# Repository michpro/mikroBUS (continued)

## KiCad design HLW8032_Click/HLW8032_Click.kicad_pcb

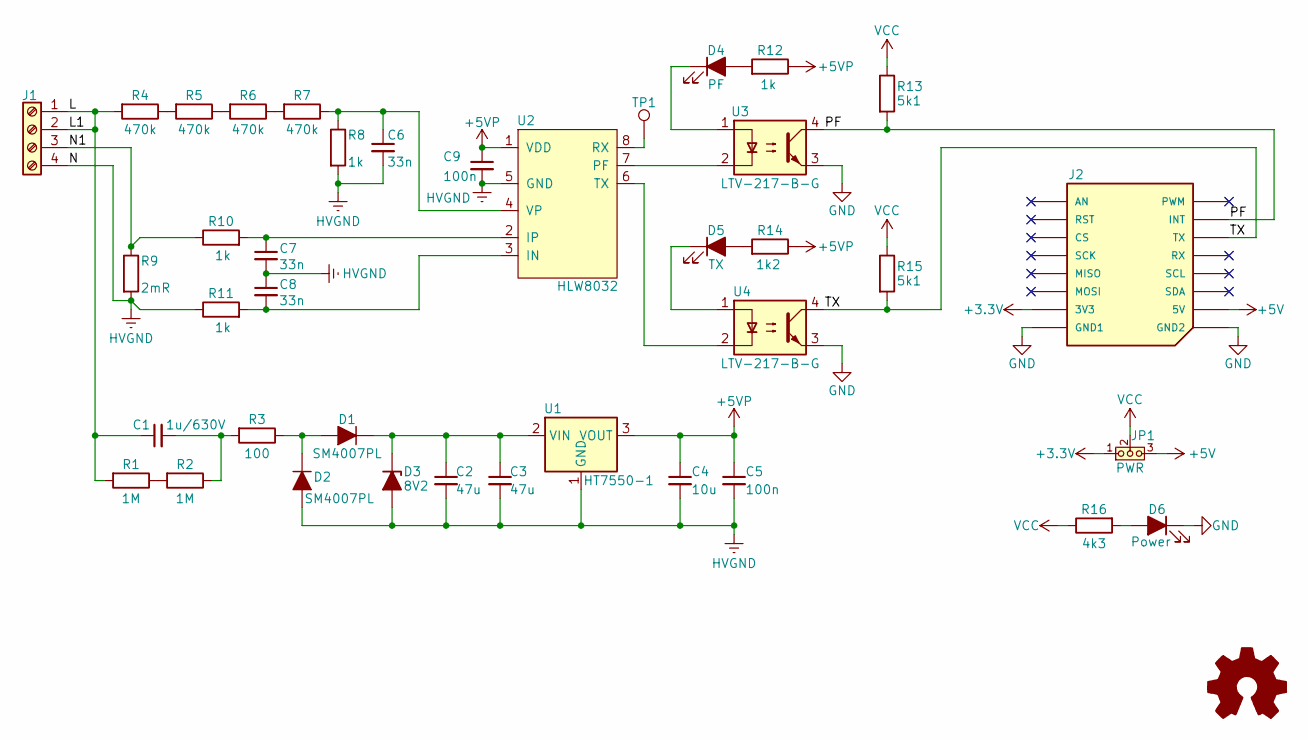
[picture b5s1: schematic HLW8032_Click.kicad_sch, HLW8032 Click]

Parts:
C1: 1u/630V; C_2220_5750Metric; LCSC C784102
C2, C3: 47u; C_1210_3225Metric; LCSC C5440143
C4: 10u; C_0805_2012Metric; LCSC C15850
C5, C9: 100n; C_0805_2012Metric; LCSC C49678
C6, C7, C8: 33n; C_0805_2012Metric; LCSC C1739
D1, D2: SM4007PL; D_SOD-123FL; LCSC C64898
D3: 8V2; D_SOD-123; LCSC C22399882
D4: PF; LED_0805_2012Metric; LCSC C2296
D5: TX; LED_0805_2012Metric; LCSC C84256
D6: Power; LED_0805_2012Metric; LCSC C2297
J1: 2EDGR-5.08-04P; LCSC C5187975
J2: HLW8032 Click v${REVISION} by MPro; mikroBUS_module_L; LCSC -----
JP1: PWR; PinHeader_1x03_P2.54mm_Vertical; LCSC C5383112
LOGO1: Logo_Open_Hardware_Small; OSHW-Logo2_7.3x6mm_SilkScreen
R1, R2: 1M; R_1206_3216Metric; LCSC C17927
R3: 100; R_2512_6332Metric; LCSC C5126189
R4, R5, R6, R7: 470k; R_0805_2012Metric; LCSC C17709
R8, R10, R11: 1k; R_0805_2012Metric; LCSC C17513
R9: 2mR; R_2512_6332Metric_HP; LCSC C316197
R12: 1k; R_0603_1608Metric; LCSC C21190
R13, R15: 5k1; R_0603_1608Metric; LCSC C23186
R14: 1k2; R_0603_1608Metric; LCSC C22765
R16: 4k3; R_0805_2012Metric; LCSC C17667
TP1: RX; TestPoint_Pad_D2.0mm; LCSC ------
U1: HT7550-1; SOT-89-3; LCSC C16106
U2: HLW8032; SOP-8_3.9x4.9mm_P1.27mm; LCSC C128023
U3, U4: LTV-217-B-G; SOP-4_4.4x2.6mm_P1.27mm; LCSC C115450

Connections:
+3.3V: J2.P7 (3V3), JP1.1 (A)
+5V: J2.P10 (5V), JP1.3 (B)
+5VP: C4.1, C5.1, C9.1, R12.1, R14.1, U1.3 (VOUT), U2.1 (VDD)
/L: C1.1, J1.1, J1.2, R1.2, R4.2
/N1: J1.3, R9.1, R10.1
/PF: J2.P15 (INT), R13.2, U3.4
/TX: J2.P14 (TX), R15.2, U4.4
GND: D6.1 (K), J2.P8 (GND1), J2.P9 (GND2), U3.3, U4.3
HVGND: C2.2, C3.2, C4.2, C5.2, C6.2, C7.2, C8.1, C9.2, D2.2 (A), D3.2 (A), J1.4, R8.2, R9.2, R11.1, U1.1 (GND), U2.5 (GND)
unnamed: C1.2, R2.1, R3.2
unnamed: D1.2 (A), D2.1 (K), R3.1
unnamed: C2.1, C3.1, D1.1 (K), D3.1 (K), U1.2 (VIN)
unnamed: D4.2 (A), R12.2
unnamed: D4.1 (K), U3.1
unnamed: D5.2 (A), R14.2
unnamed: D5.1 (K), U4.1
unnamed: D6.2 (A), R16.2
unnamed: R1.1, R2.2
unnamed: R4.1, R5.2
unnamed: R5.1, R6.2
unnamed: R6.1, R7.2
unnamed: C8.2, R11.2, U2.3 (IN)
unnamed: C7.1, R10.2, U2.2 (IP)
unnamed: U2.7 (PF), U3.2
unnamed: TP1.1, U2.8 (RX)
unnamed: U2.6 (TX), U4.2
unnamed: C6.1, R7.1, R8.1, U2.4 (VP)
VCC: JP1.2 (C), R13.1, R15.1, R16.1

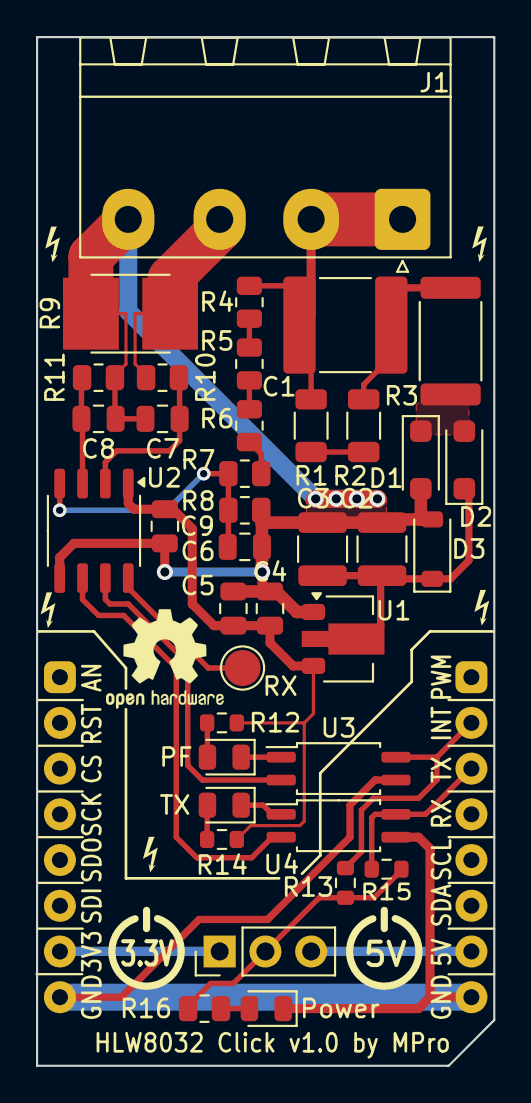
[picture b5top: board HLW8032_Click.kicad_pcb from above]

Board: 2 copper layers, 25.4 x 57.1 mm, 40 parts (0 on the bottom side), 28 nets.

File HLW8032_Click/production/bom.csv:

Designator,Footprint,Quantity,Value,LCSC Part #
C1,2220,1,1u/630V,C784102
"C2, C3",1210,2,47u,C5440143
C4,0805,1,10u,C15850
"C5, C9",0805,2,100n,C49678
"C6, C7, C8",0805,3,33n,C1739
"D1, D2",D_SOD-123FL,2,SM4007PL,C64898
D3,D_SOD-123,1,8V2,C22399882
D4,0805,1,PF,C2296
D5,0805,1,TX,C84256
D6,0805,1,Power,C2297
J1,2EDGR-5.08-04P,1,2EDGR-5.08-04P,C5187975
JP1,PinHeader_1x03_P2.54mm_Vertical,1,PWR,C5383112
"R1, R2",1206,2,1M,C17927
"R10, R11, R8",0805,3,1k,C17513
R12,0603,1,1k,C21190
"R13, R15",0603,2,5k1,C23186
R14,0603,1,1k2,C22765
R16,0805,1,4k3,C17667
R3,2512,1,100,C5126189
"R4, R5, R6, R7",0805,4,470k,C17709
R9,2512,1,2mR,C316197
U1,SOT-89-3,1,HT7550-1,C16106
U2,SOP-8_3.9x4.9mm_P1.27mm,1,HLW8032,C128023
"U3, U4",SOP-4_4.4x2.6mm_P1.27mm,2,LTV-217-B-G,C115450

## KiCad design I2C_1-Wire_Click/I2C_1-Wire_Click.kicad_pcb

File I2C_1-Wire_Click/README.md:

# **I²C to 1-Wire Click**

- [**I²C to 1-Wire Click**](#ic-to-1-wire-click)
  - [**Overview**](#overview)
    - [**Features**](#features)
  - [**Schematic diagram**](#schematic-diagram)
  - [**Module visualisation**](#module-visualisation)
  - [**Assembly**](#assembly)
  - [**Production files**](#production-files)
  - [**Configuration**](#configuration)
      - [**Note**](#note)
  - [**Reporting bugs**](#reporting-bugs)
  - [**License**](#license)
  - [**Support**](#support)

---

## **Overview**
The I²C to 1-Wire Click board is a compact module designed to enable communication between a microcontroller with an I²C interface and 1-Wire devices. Built around the DS2482-100 I²C to 1-Wire bridge IC from Analog Devices, this board simplifies the integration of 1-Wire devices into I²C-based systems. It adheres to the MikroBUS™ standard, ensuring compatibility with a wide range of host systems that support Click boards.

### **Features**
* **I²C to 1-Wire Conversion**: Utilizes the DS2482-100 chip for seamless protocol bridging.
* **MikroBUS™ Compatibility**: Equipped with a MikroBUS™ connector for easy integration into host systems.
* **1-Wire Interface**: Features a 3-pin connector for connecting 1-Wire devices.
* **Power LED**: Visual indicator for power status.
* **Flexible Power Supply**: Supports operation at both 3.3V and 5V.
* **Configurable Options**: Includes solder jumpers for I²C pull-up resistors and address selection.

---

## **Schematic diagram**

## **Module visualisation**
(click on the image to see the 3D model)
<p align="center"></p>

## **Assembly**
[Interactive BOM and placement](https://michpro.github.io/mikroBUS/I2C_1-Wire_Click/docs/ibom.html)

## **Production files**
Production files can be found [**here**](./production/).

## **Configuration**
The board offers solder jumpers for customization:
* **JP1**: Enables the 2.2kΩ pull-up resistor on SCL when closed (default: open).
* **JP2**: Enables the 2.2kΩ pull-up resistor on SDA when closed (default: open).
* **JP4, JP5**: Configure the I²C address of the DS2482-100 by connecting AD1 and AD0 to V<sub>CC</sub> or GND.

#### **Note**
To enable a pull-up feature (JP1, JP2), solder the jumper pads closed. Ensure the host system’s I²C bus requirements align with the configured settings (e.g., pull-up resistors may already exist on the host).

---

## **Reporting bugs**

[Create an issue on GitHub](https://github.com/michpro/mikroBUS/issues)

---

## **License**
Copyright © 2023-2025 Michal Protasowicki

This project is released under CERN Open Hardware Licence Version 2 - Permissive.

---

## **Support**
If You find my projects interesting and You wanted to support my work, You can give me a cup of coffee or a keg of beer :)

&nbsp;&nbsp;&nbsp;&nbsp;&nbsp;&nbsp;&nbsp;&nbsp;&nbsp;&nbsp;

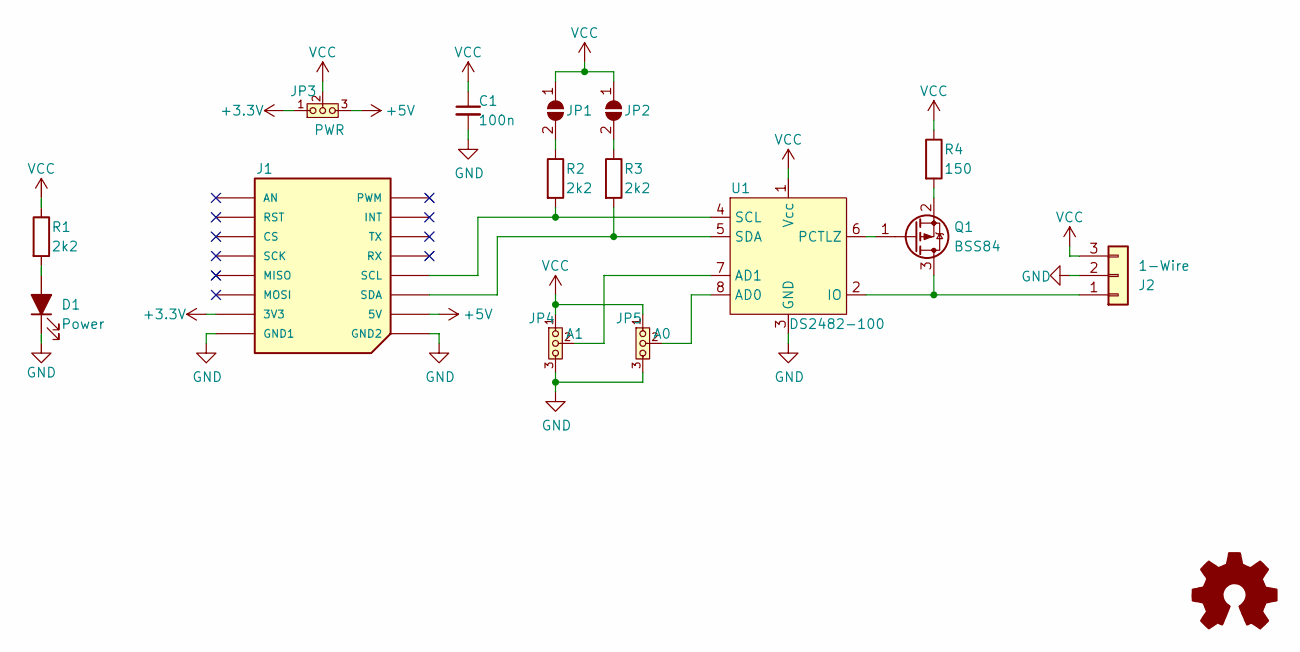
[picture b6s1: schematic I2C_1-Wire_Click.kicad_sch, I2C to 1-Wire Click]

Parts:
C1: 100n; C_0805_2012Metric; LCSC C49678
D1: Power; LED_0805_2012Metric; LCSC C2296
J1: I^{2}C to 1-Wire Click v${REVISION} by MPro; mikroBUS_module_M; LCSC -----
J2: 1-Wire; PinHeader_1x03_P2.54mm_Horizontal; LCSC -----
JP1: SCL; SolderJumper-2_P1.3mm_Open_TrianglePad1.0x1.5mm; LCSC -----
JP2: SDA; SolderJumper-2_P1.3mm_Open_TrianglePad1.0x1.5mm; LCSC -----
JP3: PWR; PinHeader_1x03_P2.54mm_Vertical; LCSC -----
JP4: A1; PinHeader_1x03_P2.54mm_Vertical; LCSC -----
JP5: A0; PinHeader_1x03_P2.54mm_Vertical; LCSC -----
LOGO1: Logo_Open_Hardware_Small; OSHW-Logo2_7.3x6mm_SilkScreen
Q1: BSS84; SOT-23; LCSC C8492
R1, R2, R3: 2k2; R_0805_2012Metric; LCSC C17520
R4: 150; R_0805_2012Metric; LCSC C17471
U1: DS2482-100; SO-8_3.9x4.9mm_P1.27mm; LCSC C143306

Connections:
+3.3V: J1.P7 (3V3), JP3.1 (A)
+5V: J1.P10 (5V), JP3.3 (B)
GND: C1.2, D1.1 (K), J1.P8 (GND1), J1.P9 (GND2), J2.2, JP4.3 (B), JP5.3 (B), U1.3 (GND)
unnamed: D1.2 (A), R1.2
unnamed: J1.P12 (SCL), R2.2, U1.4 (SCL)
unnamed: J1.P11 (SDA), R3.2, U1.5 (SDA)
unnamed: J2.1, Q1.3 (D), U1.2 (IO)
unnamed: JP1.2 (B), R2.1
unnamed: JP2.2 (B), R3.1
unnamed: JP4.2 (C), U1.7 (AD1)
unnamed: JP5.2 (C), U1.8 (AD0)
unnamed: Q1.1 (G), U1.6 (PCTLZ)
unnamed: Q1.2 (S), R4.2
VCC: C1.1, J2.3, JP1.1 (A), JP2.1 (A), JP3.2 (C), JP4.1 (A), JP5.1 (A), R1.1, R4.1, U1.1 (Vcc)

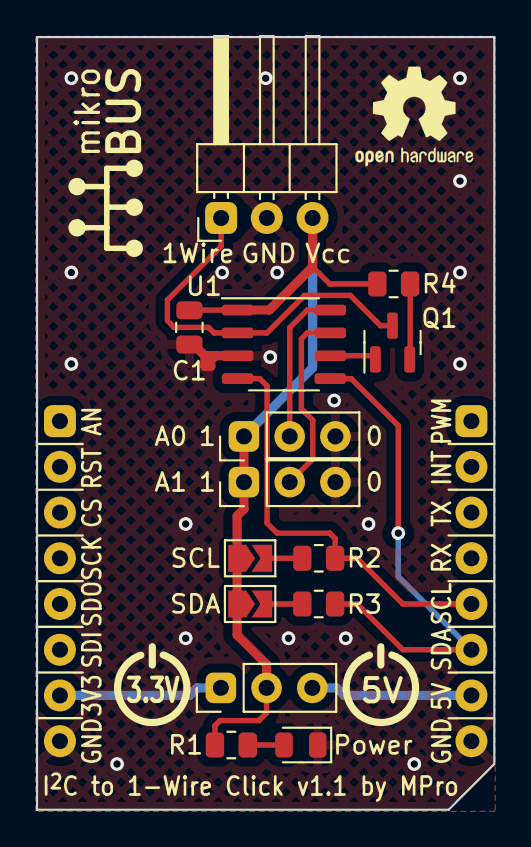
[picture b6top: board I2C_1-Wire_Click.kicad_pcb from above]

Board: 2 copper layers, 25.4 x 42.9 mm, 19 parts (0 on the bottom side), 14 nets.

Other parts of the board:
REF1: LOGO; Logo_Power_3V3
REF2: LOGO; Logo_Power_5V
REF3: mikroBUS_logo_text

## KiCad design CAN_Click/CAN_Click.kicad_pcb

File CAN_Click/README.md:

# **CAN Click**

- [**CAN Click**](#can-click)
  - [**Overview**](#overview)
    - [**Features**](#features)
  - [**Schematic diagram**](#schematic-diagram)
  - [**Module visualisation**](#module-visualisation)
  - [**Assembly**](#assembly)
  - [**Production files**](#production-files)
  - [**Testing out the hardware**](#testing-out-the-hardware)
    - [1. Hardware Setup](#1-hardware-setup)
      - [MikroBUS™ Slot Configuration](#mikrobus-slot-configuration)
      - [CAN Bus Connection](#can-bus-connection)
      - [Additional Notes](#additional-notes)
    - [2. Software Setup](#2-software-setup)
      - [Prerequisites](#prerequisites)
      - [Library Installation](#library-installation)
      - [Code Upload](#code-upload)
      - [Serial Monitor](#serial-monitor)
      - [Additional Notes](#additional-notes-1)
    - [3. Operation](#3-operation)
      - [CAN Initialization](#can-initialization)
      - [Message Transmission](#message-transmission)
      - [Message Reception](#message-reception)
    - [4. Additional Notes](#4-additional-notes)
      - [CAN Configuration](#can-configuration)
      - [Troubleshooting](#troubleshooting)
  - [**Reporting bugs**](#reporting-bugs)
  - [**License**](#license)
    - [**Hardware**](#hardware)
    - [**Software**](#software)
  - [**Support**](#support)

---

## **Overview**
The CAN Click is a compact add-on board designed to integrate Controller Area Network (CAN) bus communication into microcontroller-based systems. It adheres to the mikroBUS™ standard, enabling seamless connection to any host board with a mikroBUS™ socket. The board features the MCP2515 standalone CAN controller and the COS1042T/3 high-speed CAN transceiver, providing a robust and reliable CAN bus interface.

### **Features**
* **CAN Controller**: MCP2515 with SPI interface for communication with the host microcontroller.
* **CAN Transceiver**: COS1042T/3 supporting high-speed CAN communication.
* **Crystal Oscillator**: 12 MHz crystal for precise timing of the MCP2515.
* **Power Supply**: Configurable for 3.3V or 5V operation via jumper (JP1).
* **Interfaces**: SPI communication lines, interrupt pin (INT), and reset pin (RST) via mikroBUS™; CAN bus connection via a 3-position spring terminal.
* **Indicators**: Power/activity LED (D1).
* **Termination**: Optional CAN bus termination resistor (120Ω) via jumper (JP2).

---

## **Schematic diagram**

## **Module visualisation**
(click on the image to see the 3D model)
<p align="center"></p>

## **Assembly**
[Interactive BOM and placement](https://michpro.github.io/mikroBUS/CAN_Click/docs/ibom.html)

## **Production files**
Production files can be found [**here**](./production/).

---

## **Testing out the hardware**
Below are step-by-step instructions to set up and run the provided Arduino UNO code [test_sw.ino](./test_sw/test_sw.ino) for bidirectional CAN bus communication using the MCP2515 module. The code enables periodic transmission of a 3-byte counter message with an extended CAN ID (0x0BB0DEEF) at 1000 kbps and simultaneous reception of incoming CAN messages, both logged to the serial monitor.

### 1. Hardware Setup

#### MikroBUS™ Slot Configuration
The code supports two MikroBUS™ slot configurations for connecting the MCP2515 CAN bus module to the Arduino UNO.<br>Select one slot and connect the module to the corresponding pins:

* **MOSI**: Pin 11
* **MISO**: Pin 12
* **SCK**: Pin 13
* **For Slot 1** (default, `MIKROBUS_SLOT` set to `1`):
  * **SPI Chip Select (CS)**: Pin 10
  * **CAN Interrupt (INT)**: Pin 3
  * **CAN Standby**: Pin 6

* **For Slot 2** (modify `MIKROBUS_SLOT` to `2` in the code):
  * **SPI Chip Select (CS)**: Pin 7
  * **CAN Interrupt (INT)**: Pin 2
  * **CAN Standby**: Pin 5
  
You can also use the [Arduino UNO Click Shield](../Arduino_UNO_click_shield/README.md) or [BluePill Base Board](../BluePill_base/README.md) for the connection.

#### CAN Bus Connection
* Connect the MCP2515 module’s CAN_H and CAN_L pins to the CAN bus.
* Ensure the CAN bus is properly terminated with 120Ω resistors at both ends.
* Connect the CAN bus to another CAN device configured to operate at 1000 kbps and capable of handling extended CAN IDs.

#### Additional Notes
* Verify all connections (SPI: MOSI, MISO, SCK; power: 5V, GND) between the Arduino UNO and the MCP2515 module are secure.

---

### 2. Software Setup

#### Prerequisites
* Use an Arduino board with AVR architecture (e.g., Arduino UNO), as the code includes a check (`ARDUINO_ARCH_AVR`) to enforce this.

#### Library Installation
By default, all additional libraries are provided with the program and placed in the `src` folder of the project.
* **`mcp2515_can`**: For CAN bus communication with the MCP2515 module.
  * Available via the [Arduino Library](https://docs.arduino.cc/libraries/can_bus_shield/) Manager or [GitHub](https://github.com/Seeed-Studio/Seeed_Arduino_CAN).
* **`SimplestTimer`**: For timing the periodic message transmissions.

#### Code Upload
1. Open the provided `test_sw.ino` file in the Arduino IDE.
2. Verify the `MIKROBUS_SLOT` definition (`1` or `2`) matches your hardware configuration.
3. Upload the code to the Arduino UNO.

#### Serial Monitor
* Open the Arduino IDE’s Serial Monitor.
* Set the baud rate to **115200** to view the output.

#### Additional Notes
* The libraries used in this project are marked as independent of the µC architecture, so after removing the guard and adjusting the pin mapping, you can try to run this software on µCs other than AVR, e.g. on STM32.

---

### 3. Operation

#### CAN Initialization
* Upon startup, the code initializes the MCP2515 module at **1000 kbps** with a 12 MHz clock (`MCP_12MHz`).
* If initialization fails, the serial monitor displays `"CAN init fail, retry..."` and retries every second until successful.
* Once initialized, `"CAN init OK!"` is printed.

#### Message Transmission
* Every **2.5 seconds** (`CAN_MSG_SEND_PERIOD = 2500ms`), the Arduino sends a 3-byte CAN message:
  * **CAN ID**: `0x0BB0DEEF` (extended ID format).
  * **Data**: A 24-bit counter (`txCounter`) split into three bytes (MSB to LSB), incrementing with each transmission.
* Successful transmissions are logged to the serial monitor in the format:
  ```
  TX ID: 0x0BB0DEEF  data: 0x00 0x00 0x01
  ```

#### Message Reception
* The Arduino continuously checks for incoming CAN messages.
* Received messages are logged to the serial monitor with their CAN ID and data in hexadecimal format, e.g.:
  ```
  RX ID: 0x12345678  data: 0xAA 0xBB 0xCC
  ```
* If a message has no data, only the ID is printed.

---

### 4. Additional Notes

#### CAN Configuration
* **Speed**: 1000 kbps (`CAN_1000KBPS`).
* **ID Type**: Extended IDs (`CAN_EXTENDED_ID = 1`).
* **Frame Format**: Data Frame (`CAN_STANDARD_FRAME = 0`).
* Ensure the connected CAN device matches these settings.

#### Troubleshooting
* **No Output**: Check Serial Monitor baud rate (115200), library installation, and hardware connections.
* **CAN Init Fails**: Verify pin connections, power supply, and CAN bus termination.
* **No Communication**: Confirm the other CAN device is operational and configured correctly.

---

*By following these instructions, you should successfully set up and run the CAN bus test project on your Arduino UNO with the mikroBUS™ CAN Click. The system will transmit an incrementing counter every 2.5 seconds and display both sent and received messages on the serial monitor.*

---

## **Reporting bugs**

[Create an issue on GitHub](https://github.com/michpro/mikroBUS/issues)

---

## **License**
Copyright © 2025 Michal Protasowicki

### **Hardware**
  * Hardware part of this project is released under CERN Open Hardware Licence Version 2 - Permissive.

### **Software**
  * Software part of this project is released under MIT Licence.

---

## **Support**
If You find my projects interesting and You wanted to support my work, You can give me a cup of coffee or a keg of beer :)

&nbsp;&nbsp;&nbsp;&nbsp;&nbsp;&nbsp;&nbsp;&nbsp;&nbsp;&nbsp;

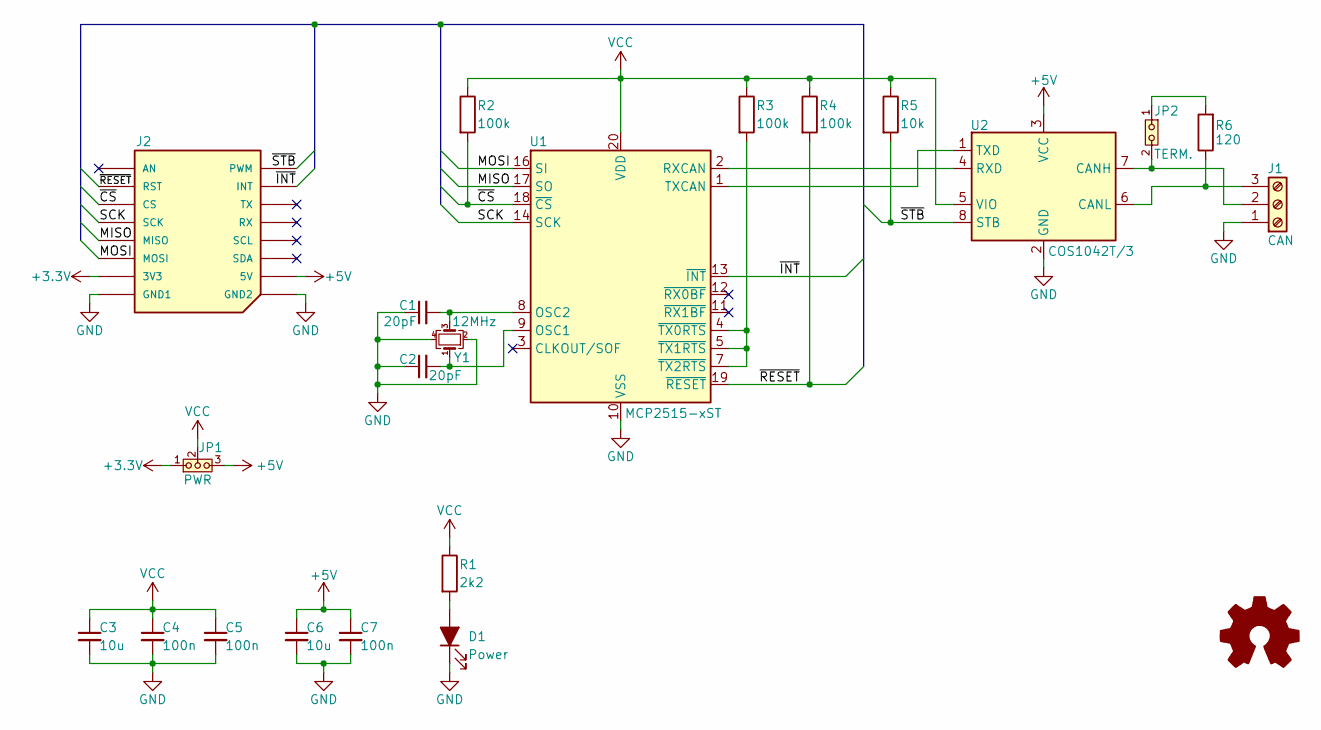
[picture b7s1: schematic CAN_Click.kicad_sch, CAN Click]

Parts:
C1, C2: 20pF; C_0805_2012Metric; LCSC C1798
C3, C6: 10u; C_0805_2012Metric; LCSC C15850
C4, C5, C7: 100n; C_0805_2012Metric; LCSC C49678
D1: Power; LED_0805_2012Metric; LCSC C2296
J1: CAN; DG250-3.5-03P-11-00AH; LCSC -----
J2: CAN Click v${REVISION} by MPro; mikroBUS_module_M; LCSC -----
JP1: PWR; PinHeader_1x03_P2.54mm_Vertical; LCSC C5383112
JP2: TERM.; PinHeader_1x02_P2.54mm_Vertical; LCSC C5383111
LOGO1: Logo_Open_Hardware_Small; OSHW-Logo2_7.3x6mm_SilkScreen
R1: 2k2; R_0805_2012Metric; LCSC C17520
R2, R3, R4: 100k; R_0805_2012Metric; LCSC C149504
R5: 10k; R_0805_2012Metric; LCSC C17414
R6: 120; R_0805_2012Metric; LCSC C17437
U1: MCP2515-xST; TSSOP-20_4.4x6.5mm_P0.65mm; LCSC C185941
U2: COS1042T/3; SOIC-8_3.9x4.9mm_P1.27mm; LCSC C5334502
Y1: 12MHz; Crystal_SMD_3225-4Pin_3.2x2.5mm; LCSC C9002

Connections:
+3.3V: J2.P7 (3V3), JP1.1 (A)
+5V: C6.1, C7.1, J2.P10 (5V), JP1.3 (B), U2.3 (VCC)
/MISO: J2.P5 (MISO), U1.17 (SO)
/MOSI: J2.P6 (MOSI), U1.16 (SI)
/SCK: J2.P4 (SCK), U1.14 (SCK)
/~CS: J2.P3 (CS), R2.2, U1.18 (~CS)
/~INT: J2.P15 (INT), U1.13 (~INT)
/~RESET: J2.P2 (RST), R4.2, U1.19 (~RESET)
/~STB: J2.P16 (PWM), R5.2, U2.8 (STB)
GND: C1.1, C2.1, C3.2, C4.2, C5.2, C6.2, C7.2, D1.1 (K), J1.1, J2.P8 (GND1), J2.P9 (GND2), U1.10 (VSS), U2.2 (GND), Y1.2, Y1.4
unnamed: D1.2 (A), R1.2
unnamed: J1.2, JP2.2 (B), U2.7 (CANH)
unnamed: J1.3, R6.1, U2.6 (CANL)
unnamed: JP2.1 (A), R6.2
unnamed: C2.2, U1.9 (OSC1), Y1.1
unnamed: C1.2, U1.8 (OSC2), Y1.3
unnamed: U1.2 (RXCAN), U2.4 (RXD)
unnamed: U1.1 (TXCAN), U2.1 (TXD)
unnamed: R3.2, U1.4 (~TX0RTS), U1.5 (~TX1RTS), U1.7 (~TX2RTS)
VCC: C3.1, C4.1, C5.1, JP1.2 (C), R1.1, R2.1, R3.1, R4.1, R5.1, U1.20 (VDD), U2.5 (VIO)

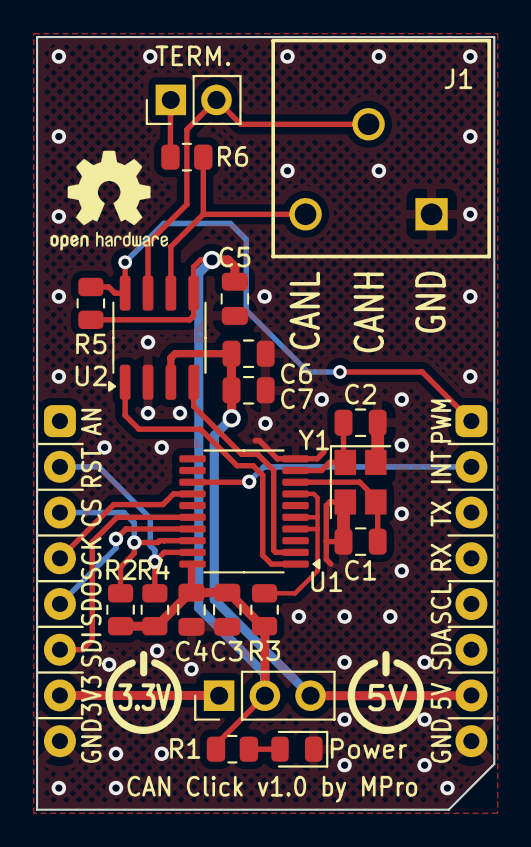
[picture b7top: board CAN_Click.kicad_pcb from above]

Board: 2 copper layers, 25.4 x 42.9 mm, 22 parts (0 on the bottom side), 20 nets.

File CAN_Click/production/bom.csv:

Designator,Footprint,Quantity,Value,LCSC Part #
"C1, C2",0805,2,20pF,C1798
"C3, C6",0805,2,10u,C15850
"C4, C5, C7",0805,3,100n,C49678
D1,0805,1,Power,C2296
J1,DG250-3.5-03P-11-00AH,1,CAN,-----
JP1,PinHeader_1x03_P2.54mm_Vertical,1,PWR,C5383112
JP2,PinHeader_1x02_P2.54mm_Vertical,1,TERM.,C5383111
R1,0805,1,2k2,C17520
"R2, R3, R4",0805,3,100k,C149504
R5,0805,1,10k,C17414
R6,0805,1,120,C17437
U1,TSSOP-20_4.4x6.5mm_P0.65mm,1,MCP2515-xST,C185941
U2,SOIC-8_3.9x4.9mm_P1.27mm,1,COS1042T/3,C5334502
Y1,Crystal_SMD_3225-4Pin_3.2x2.5mm,1,12MHz,C9002

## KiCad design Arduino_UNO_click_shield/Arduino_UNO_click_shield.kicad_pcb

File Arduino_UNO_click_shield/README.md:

# **Arduino UNO Click Shield**

- [**Arduino UNO Click Shield**](#arduino-uno-click-shield)
  - [**Overview**](#overview)
    - [**Supported boards**](#supported-boards)
    - [**Features**](#features)
    - [**Configuration Jumpers**](#configuration-jumpers)
      - [**JP3: VCC Selection**](#jp3-vcc-selection)
      - [**JP1 and JP2: I²C Configuration**](#jp1-and-jp2-ic-configuration)
      - [**JP4 and JP5: UART Configuration**](#jp4-and-jp5-uart-configuration)
  - [**Schematic diagram**](#schematic-diagram)
  - [**Module visualisation**](#module-visualisation)
  - [**Assembly**](#assembly)
  - [**Production files**](#production-files)
  - [**Reporting bugs**](#reporting-bugs)
  - [**License**](#license)
    - [**Hardware**](#hardware)
    - [**Software**](#software)
  - [**Support**](#support)

---

## **Overview**
The Arduino UNO Click Shield is an extension board designed for the Arduino UNO, enhancing its capabilities by providing a mikroBUS™ socket for connecting Click boards. Additionally, it integrates an onboard PY32F030F18P6TU microcontroller, whose task is to provide SPI to UART conversion for MikroBUS™ slot 2. This shield is ideal for hobbyists, engineers, and developers looking to expand the Arduino ecosystem with modular add-ons.

### **Supported boards**
  * **Arduino UNO** boards and clones as well as other boards compatible with the Arduino UNO R3 standard.

### **Features**
* **mikroBUS™ Socket**: Facilitates the connection of Click boards, supporting interfaces such as SPI, I²C, UART, analog, PWM, and interrupt signals.
* **Onboard PY32F030F18P6TU Microcontroller**: Features an PY32F030F18P6TU (ARM Cortex-M0, 32-bit), whose task is to provide SPI to UART conversion for MikroBUS™ slot 2.
* **Voltage Selection**: A 3-pole solder jumper (JP3) enables selection between the Arduino's IOREF voltage (typically 5V) and 3.3V for powering the Click board.
* **I²C Configuration Jumpers**: Two 2-pin jumpers (JP1 and JP2) enables the 2.2kΩ pull-up resistor on SDA and SCL.
* **SWD Connector**: A 4-pin connector (J4) for programming and debugging the onboard PY32F030 microcontroller.

---

### **Configuration Jumpers**
#### **JP3: V<sub>CC</sub> Selection**
JP3 is a 3-pole solder jumper that determines the supply voltage for the Click board's V<sub>CC</sub> pin.
* Default (Pins 1-2 Bridged): V<sub>CC</sub> connects to the Arduino's IOREF pin, typically 5V on the Arduino UNO.
* Alternative (Pins 2-3 Bridged): V<sub>CC</sub> connects to the 3.3V supply from the Arduino.
Select the appropriate configuration based on the voltage requirements of the Click board in use.
#### **JP1 and JP2: I²C Configuration**
* Enables the 2.2kΩ pull-up resistor on SDA and SCL when closed.
#### **JP4 and JP5: UART Configuration**
* Soldered jumpers, bypassing the PY32F030 chip and allowing direct transmission of Arduino RX and TX signals to the mikroBUS™ socket #2.

---

## **Schematic diagram**

## **Module visualisation**
(click on the image to see the 3D model)
<p align="center"></p>

## **Assembly**
[Interactive BOM and placement](https://michpro.github.io/mikroBUS/Arduino_UNO_click_shield/docs/ibom.html)

## **Production files**
Production files can be found [**here**](./production/).

---

## **Reporting bugs**

[Create an issue on GitHub](https://github.com/michpro/mikroBUS/issues)

---

## **License**
Copyright © 2023-2025 Michal Protasowicki

### **Hardware**
  * Hardware part of this project is released under CERN Open Hardware Licence Version 2 - Permissive.

### **Software**
  * Software part of this project is released under MIT Licence.

---

## **Support**
If You find my projects interesting and You wanted to support my work, You can give me a cup of coffee or a keg of beer :)

&nbsp;&nbsp;&nbsp;&nbsp;&nbsp;&nbsp;&nbsp;&nbsp;&nbsp;&nbsp;

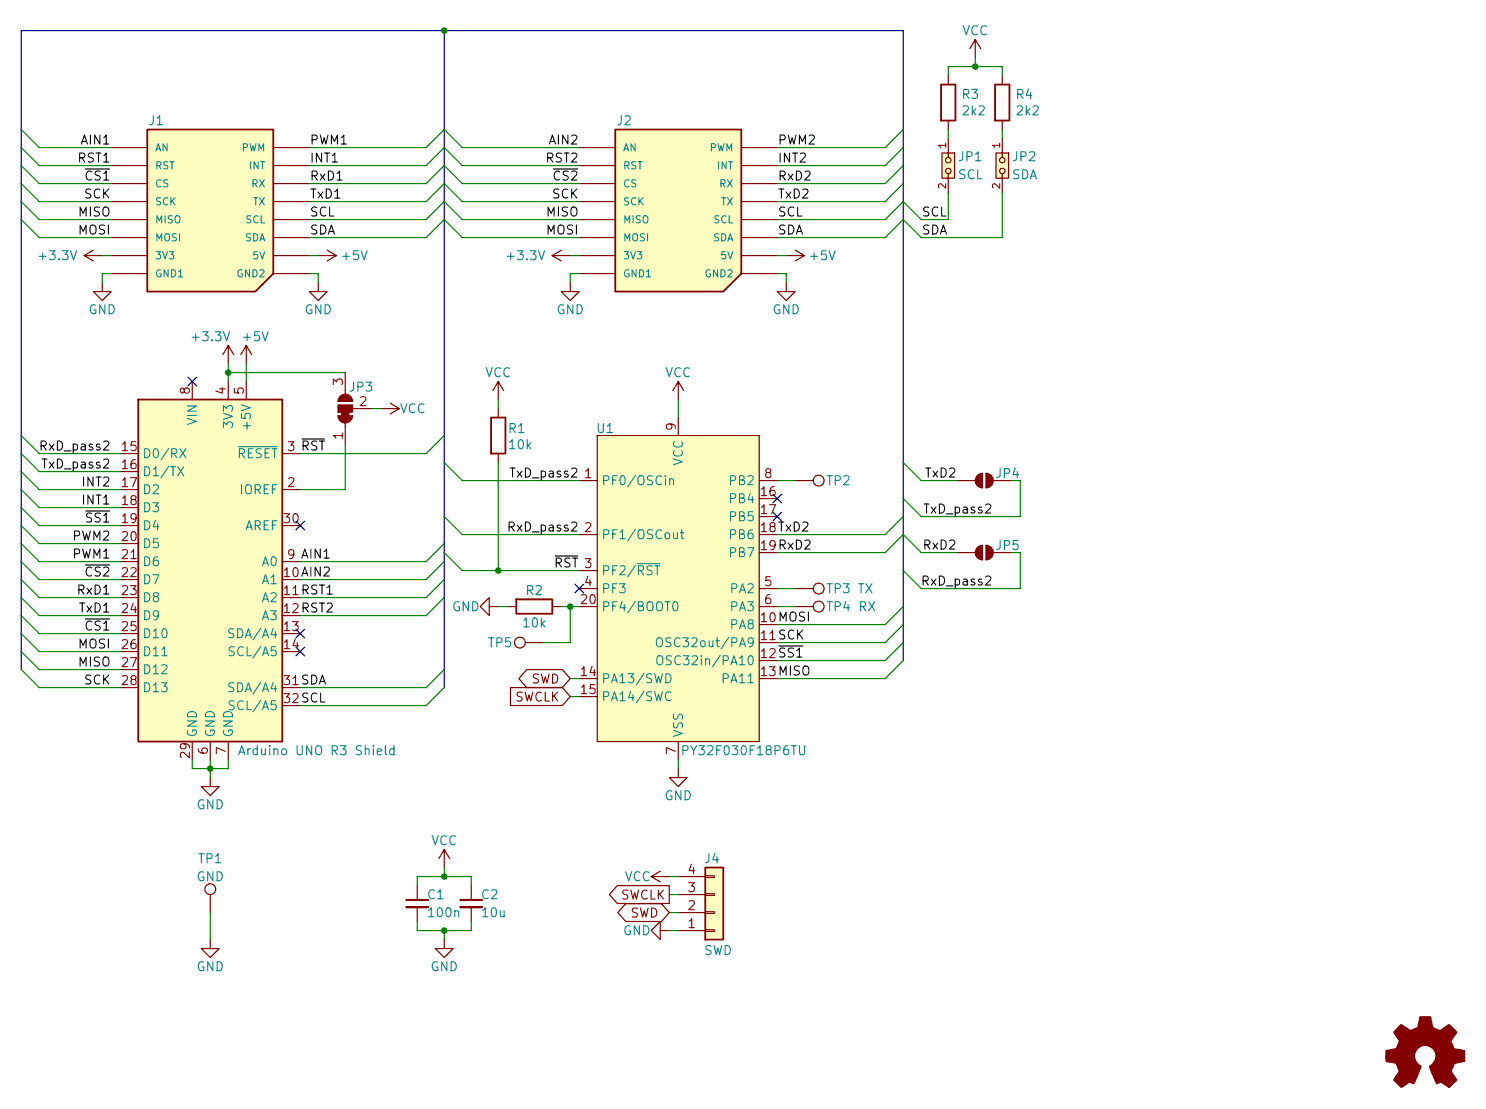
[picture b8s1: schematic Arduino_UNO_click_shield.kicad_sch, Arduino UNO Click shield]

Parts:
A1: Arduino UNO R3 Shield; Arduino_UNO_R3_WithMountingHoles_Profiled
C1: 100n; C_0805_2012Metric; LCSC C49678
C2: 10u; C_0805_2012Metric; LCSC C15850
J1, J2: mikroBUS host connector; mikroBUS_host_connector; LCSC C429957
J4: SWD; PinHeader_1x04_P2.54mm_Horizontal; LCSC C19190478
JP1: SCL; PinHeader_1x02_P2.54mm_Vertical; LCSC C27985187
JP2: SDA; PinHeader_1x02_P2.54mm_Vertical; LCSC C27985187
JP3: VCC; SolderJumper-3_P1.3mm_Bridged12_RoundedPad1.0x1.5mm
JP4: TX; SolderJumper-2_P1.3mm_Open_RoundedPad1.0x1.5mm
JP5: RX; SolderJumper-2_P1.3mm_Open_RoundedPad1.0x1.5mm
LOGO1: Logo_Open_Hardware_Small; OSHW-Logo2_7.3x6mm_SilkScreen
R1, R2: 10k; R_0805_2012Metric; LCSC C17414
R3, R4: 2k2; R_0805_2012Metric; LCSC C17520
TP1: GND; TestPoint_THTPad_D2.5mm_Drill1.2mm
TP2, TP5: TestPoint_Pad_D1.0mm
TP3: TX; TestPoint_Pad_D1.0mm
TP4: RX; TestPoint_Pad_D1.0mm
U1: PY32F030F18P6TU; TSSOP-20_4.4x6.5mm_P0.65mm; LCSC C3018715

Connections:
+3.3V: A1.4 (3V3), J1.P7 (3V3), J2.P7 (3V3), JP3.3 (B)
+5V: A1.5 (+5V), J1.P10 (5V), J2.P10 (5V)
/AIN1: A1.9 (A0), J1.P1 (AN)
/AIN2: A1.10 (A1), J2.P1 (AN)
/INT1: A1.18 (D3), J1.P15 (INT)
/INT2: A1.17 (D2), J2.P15 (INT)
/MISO: A1.27 (D12), J1.P5 (MISO), J2.P5 (MISO), U1.13 (PA11)
/MOSI: A1.26 (D11), J1.P6 (MOSI), J2.P6 (MOSI), U1.10 (PA8)
/PWM1: A1.21 (D6), J1.P16 (PWM)
/PWM2: A1.20 (D5), J2.P16 (PWM)
/RST1: A1.11 (A2), J1.P2 (RST)
/RST2: A1.12 (A3), J2.P2 (RST)
/RxD1: A1.23 (D8), J1.P14 (RX)
/RxD2: J2.P14 (RX), JP5.1 (A), U1.19 (PB7)
/RxD_pass2: A1.15 (D0/RX), JP5.2 (B), U1.2 (PF1/OSCout)
/SCK: A1.28 (D13), J1.P4 (SCK), J2.P4 (SCK), U1.11 (OSC32out/PA9)
/SCL: A1.32 (SCL/A5), J1.P12 (SCL), J2.P12 (SCL), JP1.2 (B)
/SDA: A1.31 (SDA/A4), J1.P11 (SDA), J2.P11 (SDA), JP2.2 (B)
/TxD1: A1.24 (D9), J1.P13 (TX)
/TxD2: J2.P13 (TX), JP4.1 (A), U1.18 (PB6)
/TxD_pass2: A1.16 (D1/TX), JP4.2 (B), U1.1 (PF0/OSCin)
/~CS1: A1.25 (D10), J1.P3 (CS)
/~CS2: A1.22 (D7), J2.P3 (CS)
/~RST: A1.3 (~RESET), R1.2, U1.3 (PF2/~RST)
/~SS1: A1.19 (D4), U1.12 (OSC32in/PA10)
GND: A1.6 (GND), A1.7 (GND), A1.29 (GND), C1.2, C2.2, J1.P8 (GND1), J1.P9 (GND2), J2.P8 (GND1), J2.P9 (GND2), J4.1, R2.2, TP1.1, U1.7 (VSS)
unnamed: A1.2 (IOREF), JP3.1 (A)
unnamed: JP1.1 (A), R3.2
unnamed: JP2.1 (A), R4.2
unnamed: TP3.1, U1.5 (PA2)
unnamed: TP4.1, U1.6 (PA3)
unnamed: TP2.1, U1.8 (PB2)
unnamed: R2.1, TP5.1, U1.20 (PF4/BOOT0)
SWCLK: J4.3, U1.15 (PA14/SWC)
SWD: J4.2, U1.14 (PA13/SWD)
VCC: C1.1, C2.1, J4.4, JP3.2 (C), R1.1, R3.1, R4.1, U1.9 (VCC)

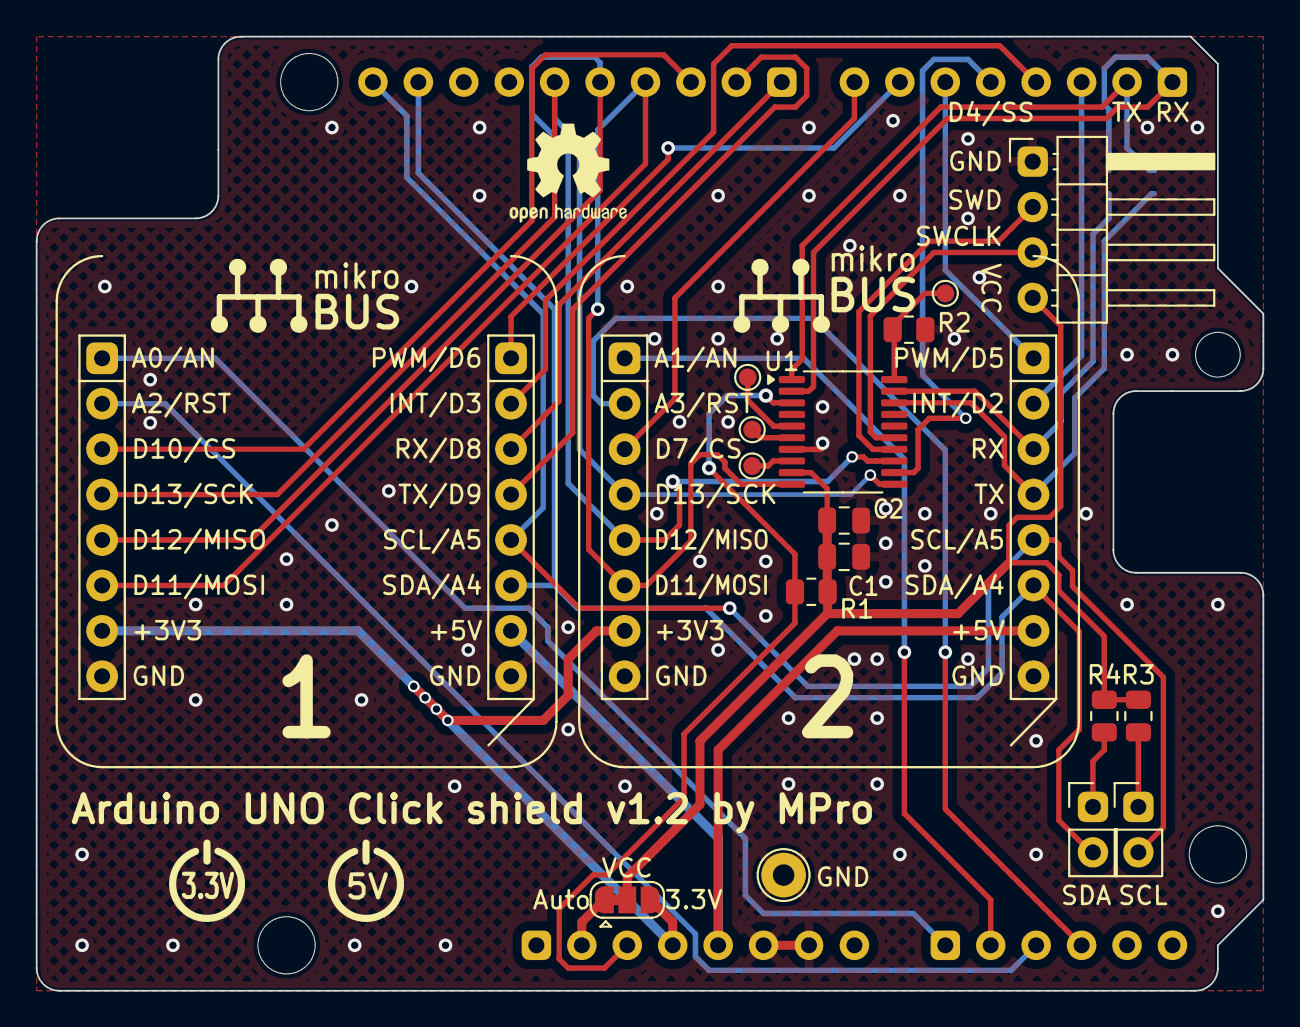
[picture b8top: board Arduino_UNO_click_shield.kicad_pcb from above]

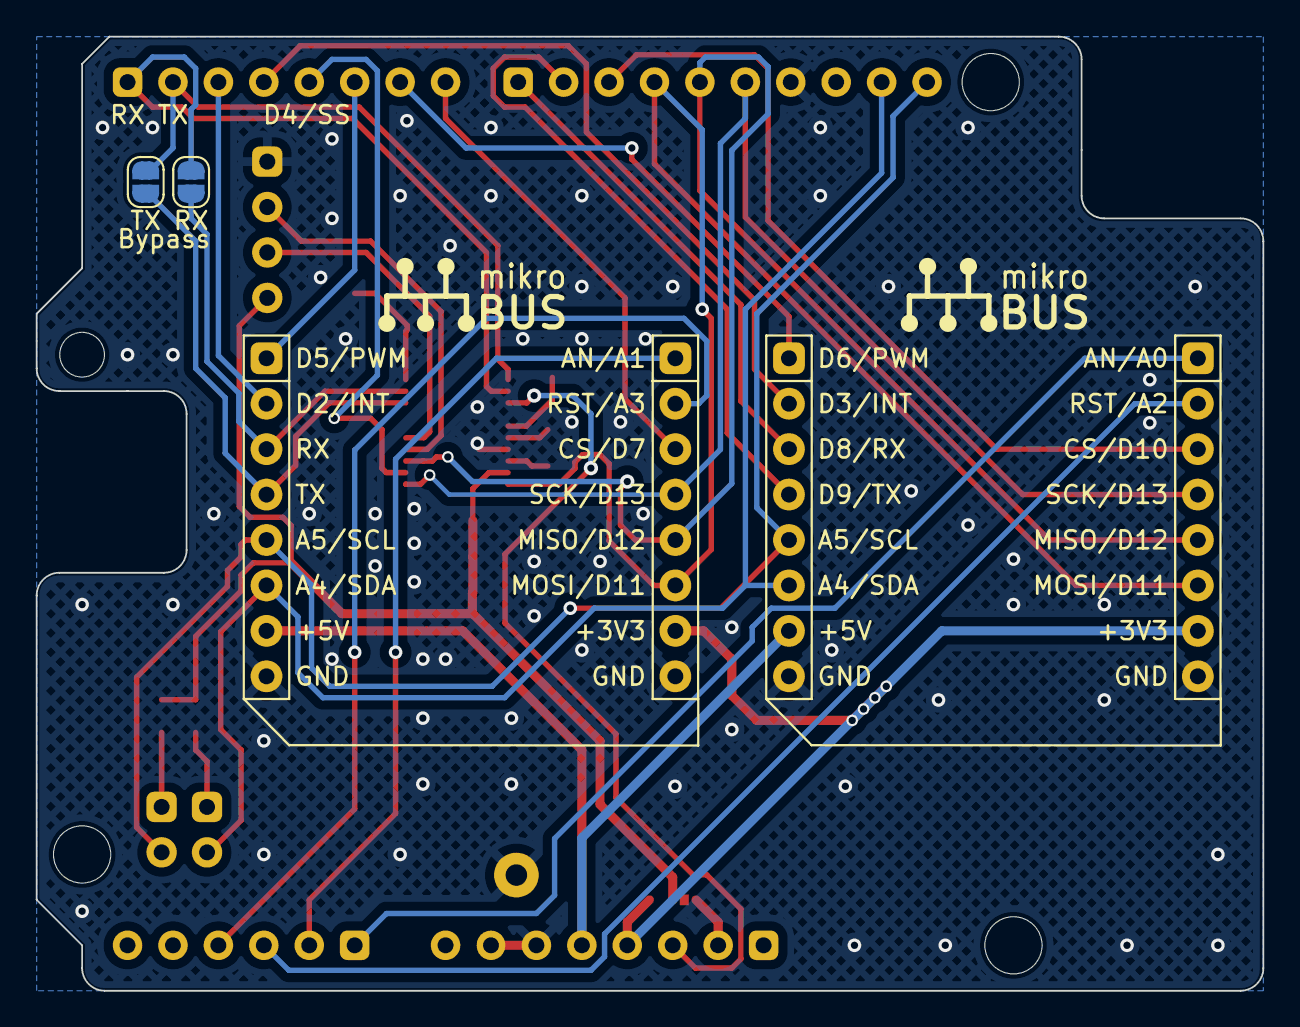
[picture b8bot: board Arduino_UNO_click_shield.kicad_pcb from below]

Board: 2 copper layers, 68.6 x 53.3 mm, 24 parts (2 on the bottom side), 36 nets.

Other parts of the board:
LOGO2: LOGO; Logo_Power_5V
LOGO3: LOGO; Logo_Power_3V3

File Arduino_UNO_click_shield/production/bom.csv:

Designator,Footprint,Quantity,Value,LCSC Part #
C1,0805,1,100n,C49678
C2,0805,1,10u,C15850
"J1, J2",mikroBUS_host_connector,2,mikroBUS host connector,C429957
J4,PinHeader_1x04_P2.54mm_Horizontal,1,SWD,C19190478
JP1,PinHeader_1x02_P2.54mm_Vertical,1,SCL,C27985187
JP2,PinHeader_1x02_P2.54mm_Vertical,1,SDA,C27985187
"R1, R2",0805,2,10k,C17414
"R3, R4",0805,2,2k2,C17520
U1,TSSOP-20_4.4x6.5mm_P0.65mm,1,PY32F030F18P6TU,C3018715

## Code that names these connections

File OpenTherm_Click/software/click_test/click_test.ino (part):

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
    if (SEL_SOCKET[0] == waitForChar(SEL_SOCKET, SEL_SOCKET_LEN))
    {
        MASTER_IN   = PA3;
        SLAVE_IN    = PB4;
        MASTER_OUT  = PA2;
        SLAVE_OUT   = PA1;
    } else
    {
        MASTER_IN   = PB11;
        SLAVE_IN    = PB3;
        MASTER_OUT  = PB10;
        SLAVE_OUT   = PB1;
    }
#else
    #error "Unsupported hardware!!!"
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
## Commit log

2023-08-29 Arduino UNO Click shield v1.0
2023-08-29 CERN-OHL-P v2 Licence
2023-08-30 Ethernet W5500 mini Click v1.0
2023-08-30 RS485 Click v1.0
2023-08-31 updated links to 3D models
2023-09-01 I2C to 1-Wire Click v1.0
2025-04-06 project files updated to Kicad version 9.0.1
2025-04-21 HW rev 1.0
2025-04-21 updated 3D models and project files
2025-04-23 Arduino UNO Click shield v1.2
2025-04-29 quartz changed to 12MHz
2025-06-01 CAN_Click test firmware for the Arduino AVR family
2025-06-09 HW rev 1.1 [corrected error in transistor Q1 connections]
2025-06-12 BluePill base board v1.0
2025-06-13 corrected thermal connection of the U2 chip
2025-07-11 OpenTherm Click v1.0
2025-07-12 LoRa Click v1.0
2025-08-07 documentation updated
2025-08-15 HLW8032 Click v1.0 - energy metering module
2025-08-20 correction of PCB thickness to 1.6 mm
2025-08-20 LIN Click v1.0
2025-09-14 RxB LED brightness adjusted
